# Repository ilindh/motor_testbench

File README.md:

<!-- KICAD_DIFF_GEN_START -->
<p align="center"><br><b>Top</b></p>
<p align="center"><br><b>Bottom</b></p>
<p align="center"><br><b>Dimensions</b></p>

<p align="center"><br><b>Schematic — Page 1</b></p>
<p align="center"><br><b>Load Cell And Temperature Measurements — Page 2</b></p>
<p align="center"><br><b>Power Regulation — Page 3</b></p>
<p align="center"><br><b>Voltage And Current Measurements — Page 4</b></p>

---
## 🛠 Technical Hardware Summary
*Autogenerated by GitHub Command Center*

### 📋 Project Overview
| Metric | Value |
| :--- | :--- |
| **Board Dimensions** | 99.5 x 79.51 mm |
| **Total Area** | 7910.75 mm² |
| **Layer Count** | 6 Copper Layers |
| **Total Components** | 286 |
| **SMD Components** | 244 |
| **THT Components** | 9 |
| **Unique Parts** | 72 |
| **DRC Status** | ⚠️ 26 Errors, 106 Warnings |
| **KiCad Version** | 10.0.4 |

### 📐 Manufacturing & DRC
| Metric | Value |
| :--- | :--- |
| **Vias** | 1443 Total (1443 TH, 0 Blind, 0 Micro) |

### 📄 Architecture
- **Digital Buses:** `ESP_UART_RX, ESP_UART_TX, ESP_USB_D+, ESP_USB_D-`
- **Power Domains:** `+3V3, GND, GNDREF`

### ⚙️ Mechanical
- **Mounting Holes:** 10 (H10 (MountingHole_3.2mm_M3), H9 (MountingHole_3.2mm_M3), H7 (MountingHole_3.2mm_M3), H1 (MountingHole_3.2mm_M3), H8 (MountingHole_3.2mm_M3), H6 (MountingHole_3.2mm_M3), H2 (MountingHole_3.2mm_M3), H5 (MountingHole_3.2mm_M3), H4 (MountingHole_3.2mm_M3), H3 (MountingHole_3.2mm_M3))

### 🚫 Do Not Populate (DNP)
- C100 (22u)
- C101 (22u)
- C105 (1u)
- C126 (1u)
- C60 (1u)
- C8 (1u)
- C99 (100p)
- R18 (22R)
- R40 (R)
- R41 (R)
- R59 (220R)
- R60 (220R)
- R61 (220R)
- R72 (10k)
- R73 (10k)
- R8 (22R)

### 📝 Project TODOs
- TODO: Check Min / Max stable capacitances for the LDOS
- TODO: FIND PROPER 6V 800mA INPUT TO 3V3 LDO
- TODO: MAADOITA NÄMÄ?
- TODO: TARKASTA PINOUT: TLV9001SIDBVRG4\n
- TODO: VAIHDA TÄHÄN\nMouser No:\n637-PSOT36\nMfr. No:\nPSOT36
- TODO:\n\nVARMISTA ETTÄ PINNIT JA FOOTPRINT OIKEAT:\nPJA3402_R1_00001\nSOT-23-3\n

### 🧠 Core ICs & Modules
| Reference | Component | Function / Description |
| :--- | :--- | :--- |
| IC6 | [MCP3564RT-E_ST](https://componentsearchengine.com/search.html?searchString=MCP3564RT-E/ST) | Analog to Digital Converters - ADC 24-bit delta-sigma ADC w/Vref, Quad channel, 3V |
| IC1 | [PJA3402_R1_00001](https://componentsearchengine.com/search.html?searchString=PJA3402_R1_00001) | MOSFETs 30V N-Channel Enhancement Mode MOSFET |
| U1 | ESP32-S3-WROOM-1 | RF Module, ESP32-S3 SoC, Wi-Fi 802.11b/g/n, Bluetooth, BLE, 32-bit, 3.3V, onboard antenna, SMD |
| U2 | OPA310SxDBV | Single Rail-to-Rail Input/Output Operational Amplifier with Shutdown, 1.5..5.5V supply, 3MHz GBW, 250uV offset voltage, 150mA output current, SOT-23-6 |
| U8 | TPS62933 | 3.8-30V, 3A Synchronous Buck Converters with pulse frequency modulation (PFM), SOT583-8 |
| IC4 | [AP7361C-33Y5-13](https://componentsearchengine.com/search.html?searchString=AP7361C-33Y5-13) | DIODES INC. - AP7361C-33Y5-13 - LDO, FIXED, 3.3V, 1A, -40 TO 85DEG C |
| U10 | OPA2387DR | Precision, 10-MHz, Low-Noise, Low-Power, RRIO, CMOS Operational Amplifier, SOIC-8 |
| IC3 | [NCV8184DR2G](https://componentsearchengine.com/search.html?searchString=NCV8184DR2G) | 70 mA Source Capability; Output Tracks within +/- 3m V; Low Input Voltage Tracking Performance (Works Down to Vref = 2.0 V); Low Dropout (0.35 V Typ.@50 mA); Low Quiescent Current; Thermal Shutdown; AEC Qualified; PPAP Capable |
| U14 | TPS7A2018PDBVRG4 | LDO Voltage Regulators 300-mA ultra-low-noi se low-IQ low-dropo |
| U9 | TPS62933 | 3.8-30V, 3A Synchronous Buck Converters with pulse frequency modulation (PFM), SOT583-8 |
| U18 | TPS7A2045PDBVR | LDO Voltage Regulators 300-mA ultra-low-noi se low-IQ low-dropo |
| IC5 | [MIE1W0505BGLVH-3R-P](https://componentsearchengine.com/search.html?searchString=MIE1W0505BGLVH-3R-P) | Isolated DC/DC Converters - SMD Next gen ultra small size isolated power module |
| U7 | MCP1502T-50E/CHY | Voltage References 50 ppm 0.1% Voltage Reference |
| U11 | TPS7A2055PDBVR | LDO Voltage Regulators 300-mA ultra-low-noi se low-IQ low-dropo |
| U16 | TPS7A2055PDBVR | LDO Voltage Regulators 300-mA ultra-low-noi se low-IQ low-dropo |
| U15 | TPS7A2050PDBVR | LDO Voltage Regulators 300-mA ultra-low-noi se low-IQ low-dropo |
| U13 | TPS7A2033PDBVR | TPS7A2033PDBVR |
| U17 | TPS7A2033PDBVR | LDO Voltage Regulators 300-mA ultra-low-noi se low-IQ low-dropo |
| U12 | TPS7A2050PDBVR | LDO Voltage Regulators 300-mA ultra-low-noi se low-IQ low-dropo |
| U3 | [CZ3723](https://componentsearchengine.com/search.html?searchString=CZ3A05) | Board Mount Current Sensors 60A Precise unipolar Coreless Current Sensor w/UL61800 |
| U6 | OPA2328DR | Precision, 10-MHz, Low-Noise, Low-Power, RRIO, CMOS Operational Amplifier, SOIC-8 |
| U4 | AMC1351DWV | Precision Reinforced Isolated Amplifier, 5V Input, 300 kHz Bandwidth, 0.4V/V, 0.2% Gain Tolerance, Differential Output, SOIC-8 |
| U5 | OPA2328DR | Precision Amplifiers Dual-channel precis ion 50-uV offset vo |

### 🔌 Connectors & Interfaces
| Reference | Type | Component | Description |
| :--- | :--- | :--- | :--- |
| J11 | Connector | Conn_01x04_Pin | Generic connector, single row, 01x04, script generated |
| J3 | Connector | Conn_01x07_Pin | Generic connector, single row, 01x07, script generated |
| J1 | Connector | USB_C_Receptacle_USB2.0_16P | USB 2.0-only 16P Type-C Receptacle connector |
| J2 | Connector | Conn_01x08_Pin | Generic connector, single row, 01x08, script generated |
| J10 | Connector | Conn_01x02_Pin | Generic connector, single row, 01x02, script generated |
| J7 | Connector | Conn_01x02_Pin | Generic connector, single row, 01x02, script generated |
| J8 | Connector | Conn_01x02_Pin | Generic connector, single row, 01x02, script generated |
| J6 | Connector | V_bat_secondary | Generic connector, single row, 01x02, script generated |
| J5 | Connector | [XT60PW-M](https://componentsearchengine.com/search.html?searchString=XT60PW-M) | Connector: DC supply; socket; XT60; male; PIN: 2; on PCBs; THT; 30A |
| J4 | Connector | [XT60PW-M](https://componentsearchengine.com/search.html?searchString=XT60PW-M) | Connector: DC supply; socket; XT60; male; PIN: 2; on PCBs; THT; 30A |

### 📏 Passive Components
| Component | Breakdown |
| :--- | :--- |
| Capacitor | 97x0603, 28x0805 and 1xOther |
| Diode | 2x0402, 2x0603 and 6xOther |
| Inductor | 1x1206 |
| Resistor | 73x0603 |

---
<!-- KICAD_DIFF_GEN_END -->

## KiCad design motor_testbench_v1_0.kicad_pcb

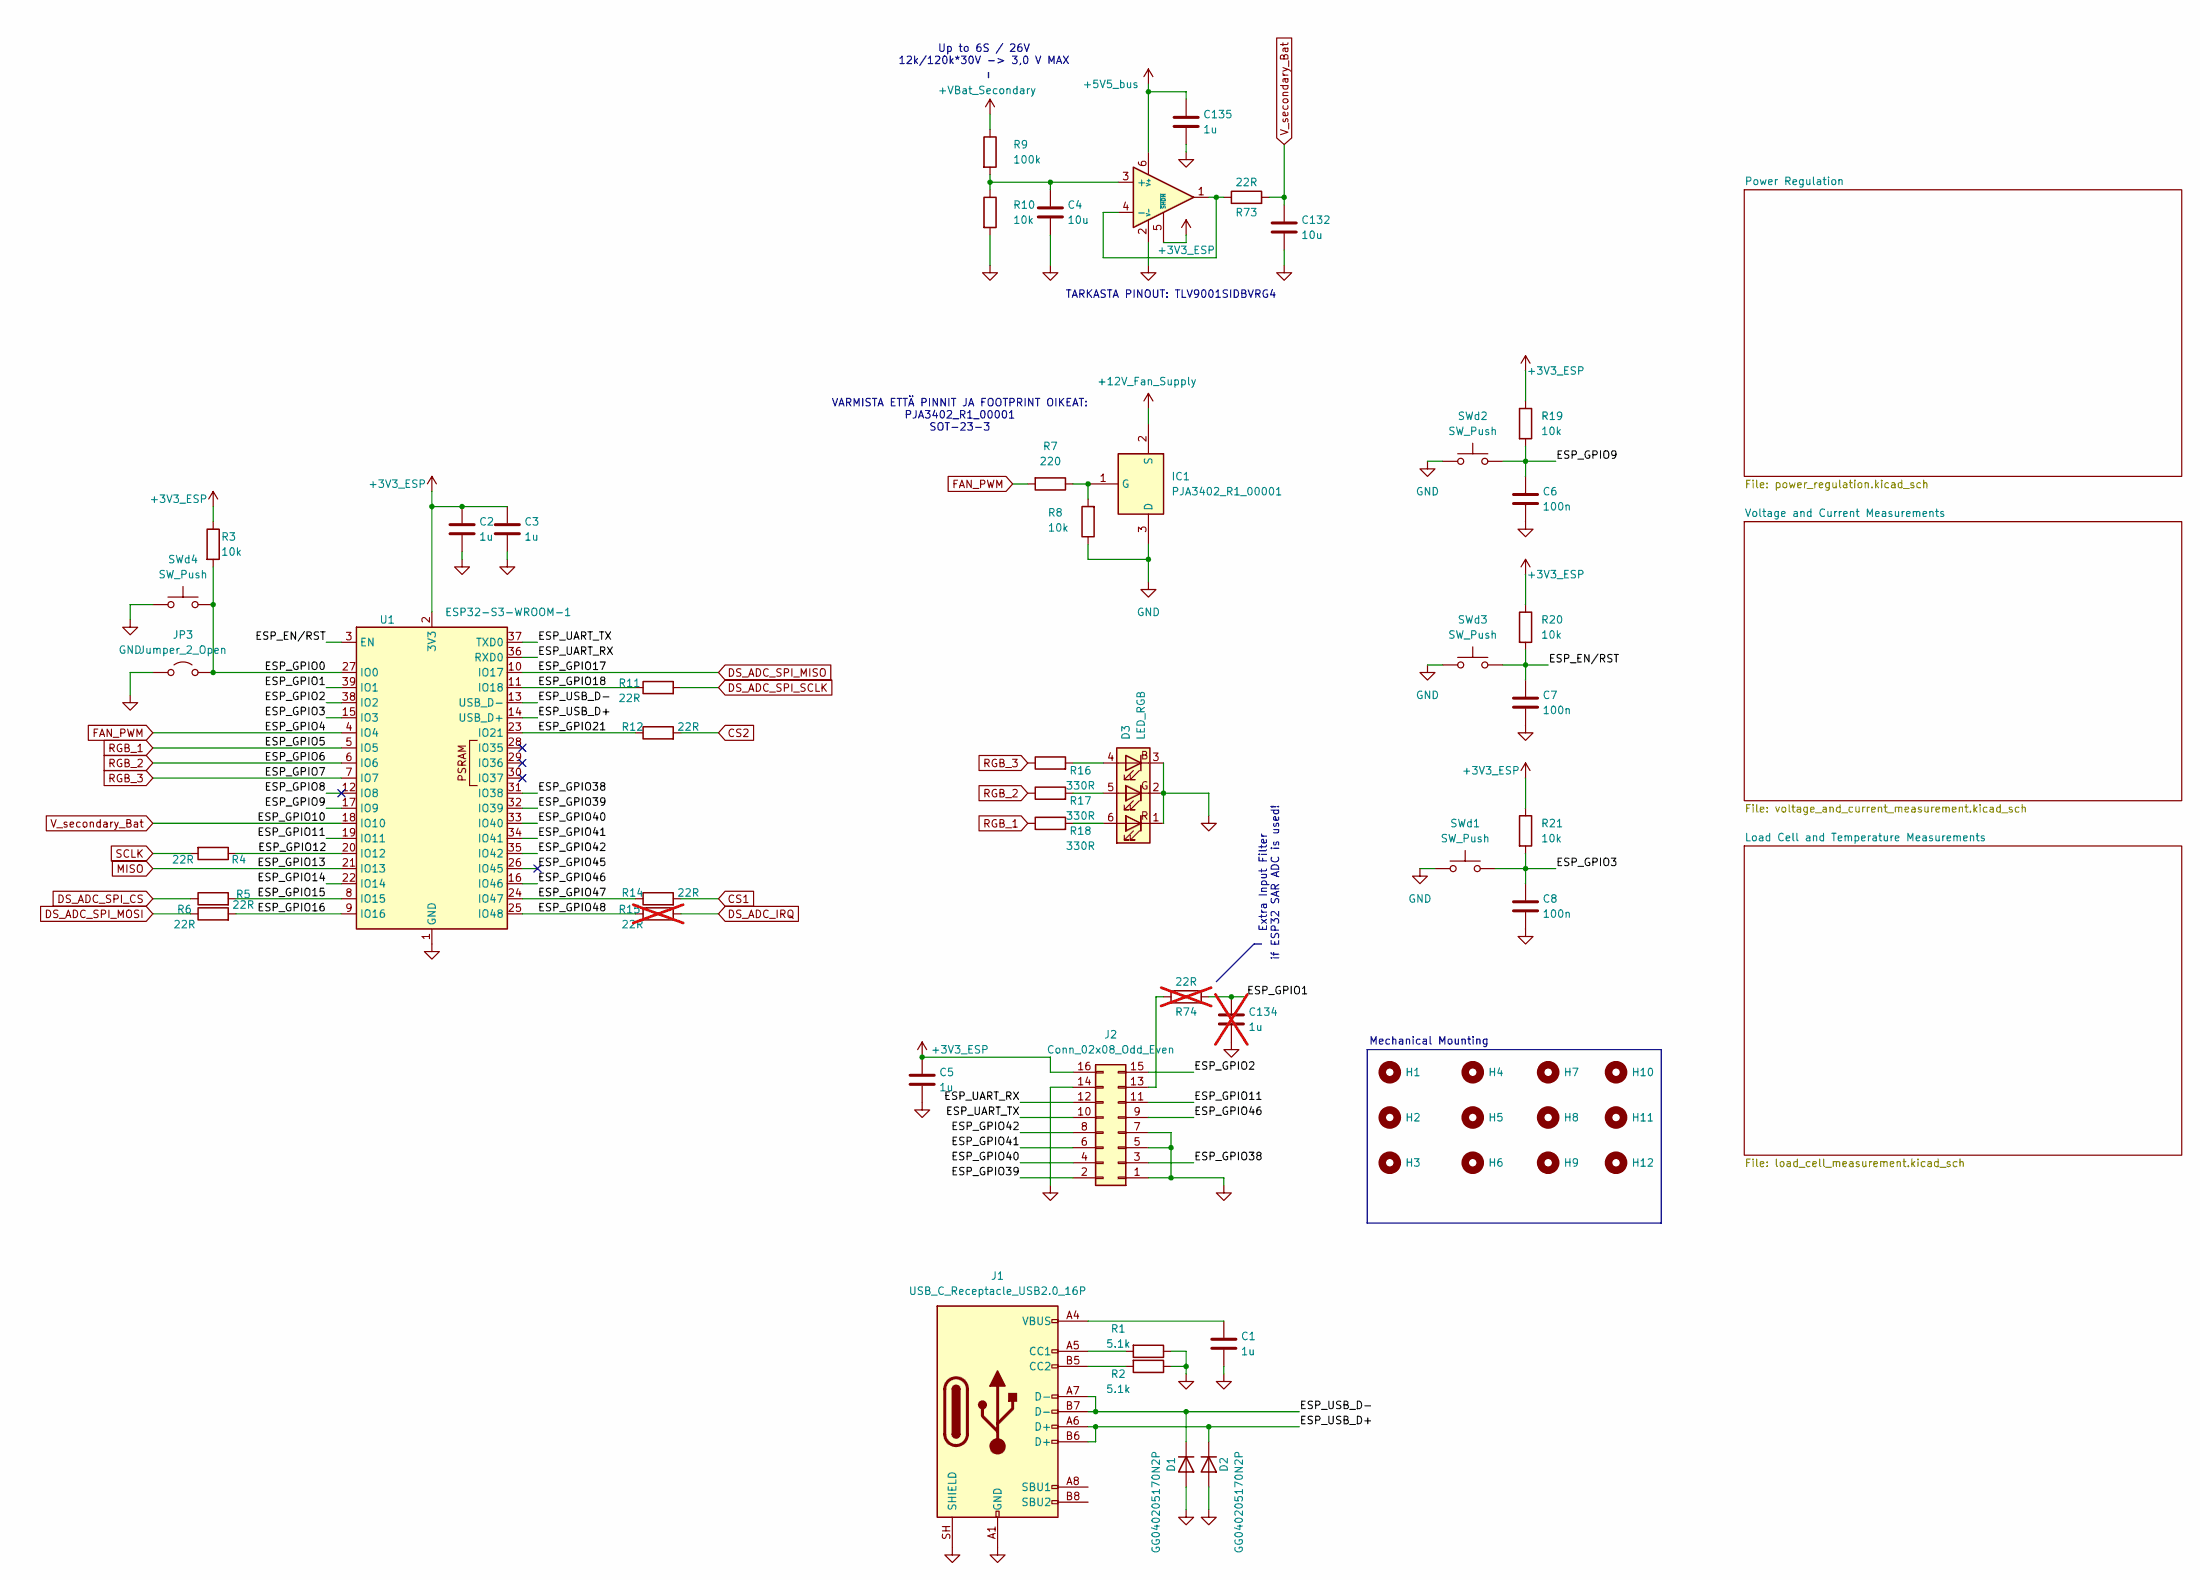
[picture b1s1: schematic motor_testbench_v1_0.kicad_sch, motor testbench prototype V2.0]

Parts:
C1, C2, C3, C5, C135: 1u; C_0603_1608Metric_Pad1.08x0.95mm_HandSolder
C4, C132: 10u; C_0603_1608Metric_Pad1.08x0.95mm_HandSolder
C6, C7, C8: 100n; C_0603_1608Metric_Pad1.08x0.95mm_HandSolder
C134: 1u; C_0603_1608Metric_Pad1.08x0.95mm_HandSolder; not fitted
D1, D2: GG040205170N2P; D_0402_1005Metric_Pad0.77x0.64mm_HandSolder
D3: LED_RGB; LED_RGB_PLCC-6
H1, H2, H3, H4, H5, H6, H7, H8, H9, H10, H11, H12: MountingHole; MountingHole_2.2mm_M2_DIN965
IC1: PJA3402_R1_00001; SOT95P240X110-3N; Manufacturer_Part_Number PJA3402_R1_00001
J1: USB_C_Receptacle_USB2.0_16P; USB_C_Receptacle_HCTL_HC-TYPE-C-16P-01A
J2: Conn_02x08_Odd_Even; PinHeader_2x08_P2.54mm_Vertical
JP3: Jumper_2_Open; SolderJumper-2_P1.3mm_Open_RoundedPad1.0x1.5mm
R1, R2: 5.1k; R_0603_1608Metric_Pad0.98x0.95mm_HandSolder
R3, R8, R10, R19, R20, R21: 10k; R_0603_1608Metric_Pad0.98x0.95mm_HandSolder
R4, R5, R6, R11, R12, R14, R73: 22R; R_0603_1608Metric_Pad0.98x0.95mm_HandSolder
R7: 220; R_0603_1608Metric_Pad0.98x0.95mm_HandSolder
R9: 100k; R_0603_1608Metric_Pad0.98x0.95mm_HandSolder
R15, R74: 22R; R_0603_1608Metric_Pad0.98x0.95mm_HandSolder; not fitted
R16, R17, R18: 330R; R_0603_1608Metric_Pad0.98x0.95mm_HandSolder
SWd1, SWd2, SWd3, SWd4: SW_Push; SW_SPST_TS-1088-xR020
U1: ESP32-S3-WROOM-1
U21: OPA310SxDBV; SOT-23-6

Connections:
+3V3_ESP: C2.1, C3.1, C5.1, J2.16, R3.1, R19.1, R20.1, R21.1, U1.2 (3V3), U21.5 (~SHDN); also elsewhere on the board
+5V5_bus: C135.1, U21.6 (V+); also elsewhere on the board
+12V_Fan_Supply: IC1.2 (S); also elsewhere on the board
+VBat_Secondary: R9.1; also elsewhere on the board
/ESP_EN/RST: C7.1, R20.2, SWd3.2, U1.3 (EN)
/ESP_GPIO0: JP3.2 (B), R3.2, SWd4.2, U1.27 (IO0)
/ESP_GPIO1: C134.1, R74.2, U1.39 (IO1)
/ESP_GPIO2: J2.15, U1.38 (IO2)
/ESP_GPIO3: C8.1, R21.2, SWd1.2, U1.15 (IO3)
/ESP_GPIO8: U1.12 (IO8)
/ESP_GPIO9: C6.1, R19.2, SWd2.2, U1.17 (IO9)
/ESP_GPIO11: J2.11, U1.19 (IO11)
/ESP_GPIO12: R4.1, U1.20 (IO12)
/ESP_GPIO14: U1.22 (IO14)
/ESP_GPIO15: R5.2, U1.8 (IO15)
/ESP_GPIO16: R6.2, U1.9 (IO16)
/ESP_GPIO18: R11.1, U1.11 (IO18)
/ESP_GPIO21: R12.1, U1.23 (IO21)
/ESP_GPIO38: J2.3, U1.31 (IO38)
/ESP_GPIO39: J2.2, U1.32 (IO39)
/ESP_GPIO40: J2.4, U1.33 (IO40)
/ESP_GPIO41: J2.6, U1.34 (IO41)
/ESP_GPIO42: J2.8, U1.35 (IO42)
/ESP_GPIO45: U1.26 (IO45)
/ESP_GPIO46: J2.9, U1.16 (IO46)
/ESP_GPIO47: R14.1, U1.24 (IO47)
/ESP_GPIO48: R15.1, U1.25 (IO48)
/ESP_UART_RX: J2.12, U1.36 (RXD0)
/ESP_UART_TX: J2.10, U1.37 (TXD0)
/ESP_USB_D+: D2.1 (K), J1.A6 (D+), J1.B6 (D+), U1.14 (USB_D+)
/ESP_USB_D-: D1.1 (K), J1.A7 (D-), J1.B7 (D-), U1.13 (USB_D-)
CS1: R14.2; also elsewhere on the board
CS2: R12.2; also elsewhere on the board
DS_ADC_IRQ: R15.2; also elsewhere on the board
DS_ADC_SPI_CS: R5.1; also elsewhere on the board
DS_ADC_SPI_MISO: U1.10 (IO17); also elsewhere on the board
DS_ADC_SPI_MOSI: R6.1; also elsewhere on the board
DS_ADC_SPI_SCLK: R11.2; also elsewhere on the board
FAN_PWM: R7.2, U1.4 (IO4)
GND: C1.2, C2.2, C3.2, C4.2, C5.2, C6.2, C7.2, C8.2, C132.2, C134.2, C135.2, D1.2 (A), D2.2 (A), D3.1 (RK), D3.2 (GK), D3.3 (BK), IC1.3 (D), J1.A1 (GND), J1.A12 (GND), J1.B1 (GND), J1.B12 (GND), J1.SH (SHIELD), J2.1, J2.5, J2.7, J2.14, JP3.1 (A), R1.1, R2.1, R8.1, R10.2, SWd1.1, SWd2.1, SWd3.1, SWd4.1, U1.1 (GND), U1.40 (GND), U1.41 (GND), U21.2 (V-); also elsewhere on the board
MISO: U1.21 (IO13); also elsewhere on the board
unnamed: C1.1, J1.A4 (VBUS), J1.A9 (VBUS), J1.B4 (VBUS), J1.B9 (VBUS)
unnamed: D3.4 (BA), R16.2
unnamed: D3.5 (GA), R17.2
unnamed: D3.6 (RA), R18.2
unnamed: IC1.1 (G), R7.1, R8.2
unnamed: J1.A5 (CC1), R1.2
unnamed: J1.B5 (CC2), R2.2
unnamed: J2.13, R74.1
unnamed: C4.1, R9.2, R10.1, U21.3 (+)
unnamed: R73.1, U21.1, U21.4 (-)
RGB_1: R18.1, U1.5 (IO5)
RGB_2: R17.1, U1.6 (IO6)
RGB_3: R16.1, U1.7 (IO7)
SCLK: R4.2; also elsewhere on the board
V_secondary_Bat: C132.1, R73.2, U1.18 (IO10)

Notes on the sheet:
Extra Input Filter if ESP32 SAR ADC is used!
Mechanical Mounting
TARKASTA PINOUT: TLV9001SIDBVRG4
VARMISTA ETTÄ PINNIT JA FOOTPRINT OIKEAT: PJA3402_R1_00001 SOT-23-3
Up to 6S / 26V 12k/120k*30V -> 3,0 V MAX

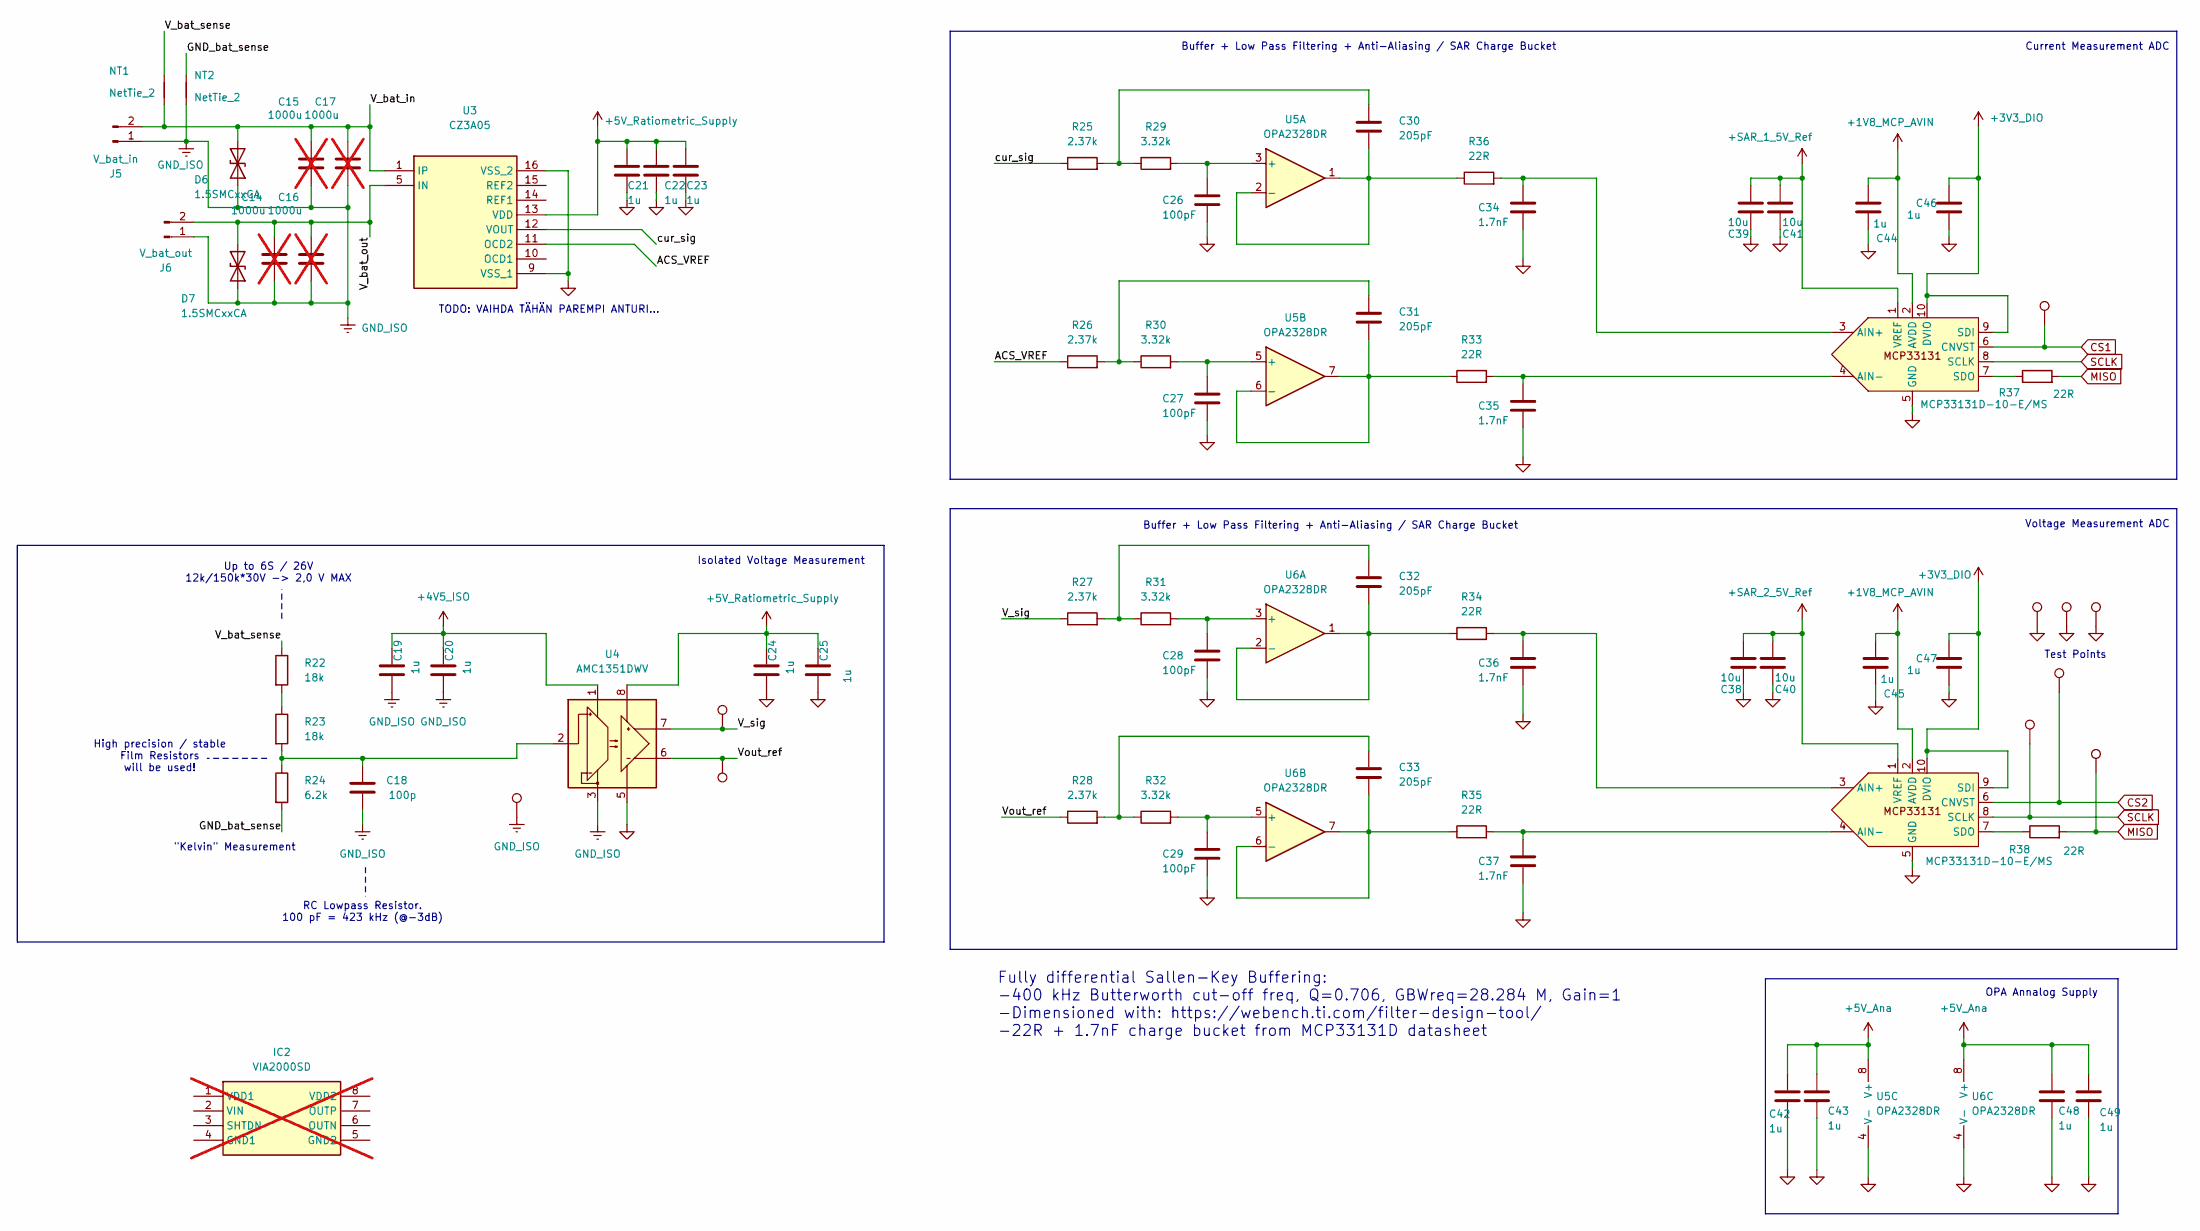
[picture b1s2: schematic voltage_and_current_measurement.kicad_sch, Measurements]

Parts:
C14, C15, C16, C17: 1000u; C_Radial_D8.0mm_H11.5mm_P3.50mm; not fitted
C18: 100p; C_0603_1608Metric_Pad1.08x0.95mm_HandSolder
C19, C20, C21, C22, C23, C24, C25, C42, C43, C44, C45, C46, C47, C48, C49: 1u; C_0603_1608Metric_Pad1.08x0.95mm_HandSolder
C26, C27, C28, C29: 100pF; C_0603_1608Metric_Pad1.08x0.95mm_HandSolder
C30, C31, C32, C33: 205pF; C_0603_1608Metric_Pad1.08x0.95mm_HandSolder
C34, C35, C36, C37: 1.7nF; C_0603_1608Metric_Pad1.08x0.95mm_HandSolder
C38, C39, C40, C41: 10u; C_0603_1608Metric_Pad1.08x0.95mm_HandSolder
CS1, CS2: TestPoint; TestPoint_Pad_D1.0mm
D6, D7: 1.5SMCxxCA; D_SMC
Dout1: TestPoint; TestPoint_Pad_D1.0mm
GND1, GND2, GND3, GND4: TestPoint; TestPoint_Pad_D1.0mm
IC2: VIA2000SD; SOIC127P1150X280-8N; Manufacturer_Part_Number VIA2000SD; not fitted
J5: V_bat_in; AMASS_XT60PW-M_1x02_P7.20mm_Horizontal_with3DModel
J6: V_bat_out; AMASS_XT60PW-M_1x02_P7.20mm_Horizontal_with3DModel
MCP1, MCP2: MCP33131D-10-E/MS; MSOP-10_3x3mm_P0.5mm
NT1, NT2: NetTie_2; NetTie-2_SMD_Pad0.5mm
R22, R23: 18k; R_0603_1608Metric_Pad0.98x0.95mm_HandSolder
R24: 6.2k; R_0603_1608Metric_Pad0.98x0.95mm_HandSolder
R25, R26, R27, R28: 2.37k; R_0603_1608Metric_Pad0.98x0.95mm_HandSolder
R29, R30, R31, R32: 3.32k; R_0603_1608Metric_Pad0.98x0.95mm_HandSolder
R33, R34, R35, R36, R37, R38: 22R; R_0603_1608Metric_Pad0.98x0.95mm_HandSolder
SCLK1: TestPoint; TestPoint_Pad_D1.0mm
U3: CZ3A05; Manufacturer_Part_Number CZ3A05; Mouser Part Number 412-CZ3A05
U4: AMC1351DWV; SOIC-8_7.5x5.85mm_P1.27mm
U5: OPA2328DR; SOIC-8_3.9x4.9mm_P1.27mm
U6: OPA2328DR; SOIC-8_3.9x4.9mm_P1.27mm; Mouser No: 595-OPA2328DR
Vsig1, Vsig2: TestPoint; TestPoint_Pad_D1.0mm

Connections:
+1V8_MCP_AVIN: C44.2, C45.2, MCP1.2 (AVDD), MCP2.2 (AVDD); also elsewhere on the board
+3V3_DIO: C46.1, C47.1, MCP1.9 (SDI), MCP1.10 (DVIO), MCP2.9 (SDI), MCP2.10 (DVIO); also elsewhere on the board
+4V5_ISO: C19.1, C20.1, U4.1 (VDD1); also elsewhere on the board
+5V_Ana: C42.1, C43.1, C48.1, C49.1, U5.8 (V+), U6.8 (V+); also elsewhere on the board
+5V_Ratiometric_Supply: C21.1, C22.1, C23.1, C24.1, C25.1, U3.13 (VDD), U4.8 (VDD2); also elsewhere on the board
+SAR_1_5V_Ref: C39.1, C41.1, MCP1.1 (VREF); also elsewhere on the board
+SAR_2_5V_Ref: C38.1, C40.1, MCP2.1 (VREF); also elsewhere on the board
/Voltage and Current Measurements/ACS_VREF: R26.1, U3.11 (OCD2); also elsewhere on the board
/Voltage and Current Measurements/GND_bat_sense: NT2.2, R24.2
/Voltage and Current Measurements/V_bat_in: C15.1, C17.1, D6.2 (A2), J5.2, NT1.1, U3.1 (IP)
/Voltage and Current Measurements/V_bat_out: C14.1, C16.1, D7.2 (A2), J6.2, U3.5 (IN)
/Voltage and Current Measurements/V_bat_sense: NT1.2, R22.1
/Voltage and Current Measurements/V_sig: R27.1, U4.7 (OUTP), Vsig1.1 (1_1)
/Voltage and Current Measurements/Vout_ref: R28.1, U4.6 (OUTN), Vsig2.1 (1_1)
/Voltage and Current Measurements/cur_sig: R25.1, U3.12 (VOUT); also elsewhere on the board
CS1: CS1.1 (1_1), MCP1.6 (CNVST); also elsewhere on the board
CS2: CS2.1 (1_1), MCP2.6 (CNVST); also elsewhere on the board
GND: C21.2, C22.2, C23.2, C24.2, C25.2, C26.2, C27.2, C28.2, C29.2, C34.2, C35.2, C36.2, C37.2, C38.2, C39.2, C40.2, C41.2, C42.2, C43.2, C44.1, C45.1, C46.2, C47.2, C48.2, C49.2, GND2.1 (1_1), GND3.1 (1_1), GND4.1 (1_1), MCP1.5 (GND), MCP2.5 (GND), U3.9 (VSS_1), U3.16 (VSS_2), U4.5 (GND2), U5.4 (V-), U6.4 (V-); also elsewhere on the board
GND_ISO: C14.2, C15.2, C16.2, C17.2, C18.2, C19.2, C20.2, D6.1 (A1), D7.1 (A1), GND1.1 (1_1), J5.1, J6.1, NT2.1, U4.3 (GND1), U4.4 (GND1); also elsewhere on the board
MISO: Dout1.1 (1_1), R37.2, R38.2; also elsewhere on the board
unnamed: C30.1, R25.2, R29.1
unnamed: C31.1, R26.2, R30.1
unnamed: C32.1, R27.2, R31.1
unnamed: C33.1, R28.2, R32.1
unnamed: C34.1, MCP1.3 (AIN+), R36.2
unnamed: C35.1, MCP1.4 (AIN-), R33.2
unnamed: MCP1.7 (SDO), R37.1
unnamed: C36.1, MCP2.3 (AIN+), R34.2
unnamed: C37.1, MCP2.4 (AIN-), R35.2
unnamed: MCP2.7 (SDO), R38.1
unnamed: R22.2, R23.1
unnamed: C18.1, R23.2, R24.1, U4.2 (IN)
unnamed: C26.1, R29.2, U5.3 (+)
unnamed: C30.2, R36.1, U5.1, U5.2 (-)
unnamed: C27.1, R30.2, U5.5 (+)
unnamed: C31.2, R33.1, U5.6 (-), U5.7
unnamed: C28.1, R31.2, U6.3 (+)
unnamed: C32.2, R34.1, U6.1, U6.2 (-)
unnamed: C29.1, R32.2, U6.5 (+)
unnamed: C33.2, R35.1, U6.6 (-), U6.7
SCLK: MCP1.8 (SCLK), MCP2.8 (SCLK), SCLK1.1 (1_1); also elsewhere on the board

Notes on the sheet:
RC Lowpass Resistor. 100 pF = 423 kHz (@-3dB)
TODO: VAIHDA TÄHÄN PAREMPI ANTURI...
Up to 6S / 26V 12k/150k*30V -> 2,0 V MAX
OPA Annalog Supply
Voltage Measurement ADC
Buffer + Low Pass Filtering + Anti-Aliasing / SAR Charge Bucket
Isolated Voltage Measurement
Current Measurement ADC
Test Points
High precision / stable Film Resistors will be used!
Fully differential Sallen-Key Buffering: -400 kHz Butterworth cut-off freq, Q=0.706, GBWreq=28.284 M, Gain=1 -Dimensioned with: https://webench.ti.com/filter-design-tool/ -22R + 1.7nF charge bucket from MCP33131D datasheet
"Kelvin" Measurement

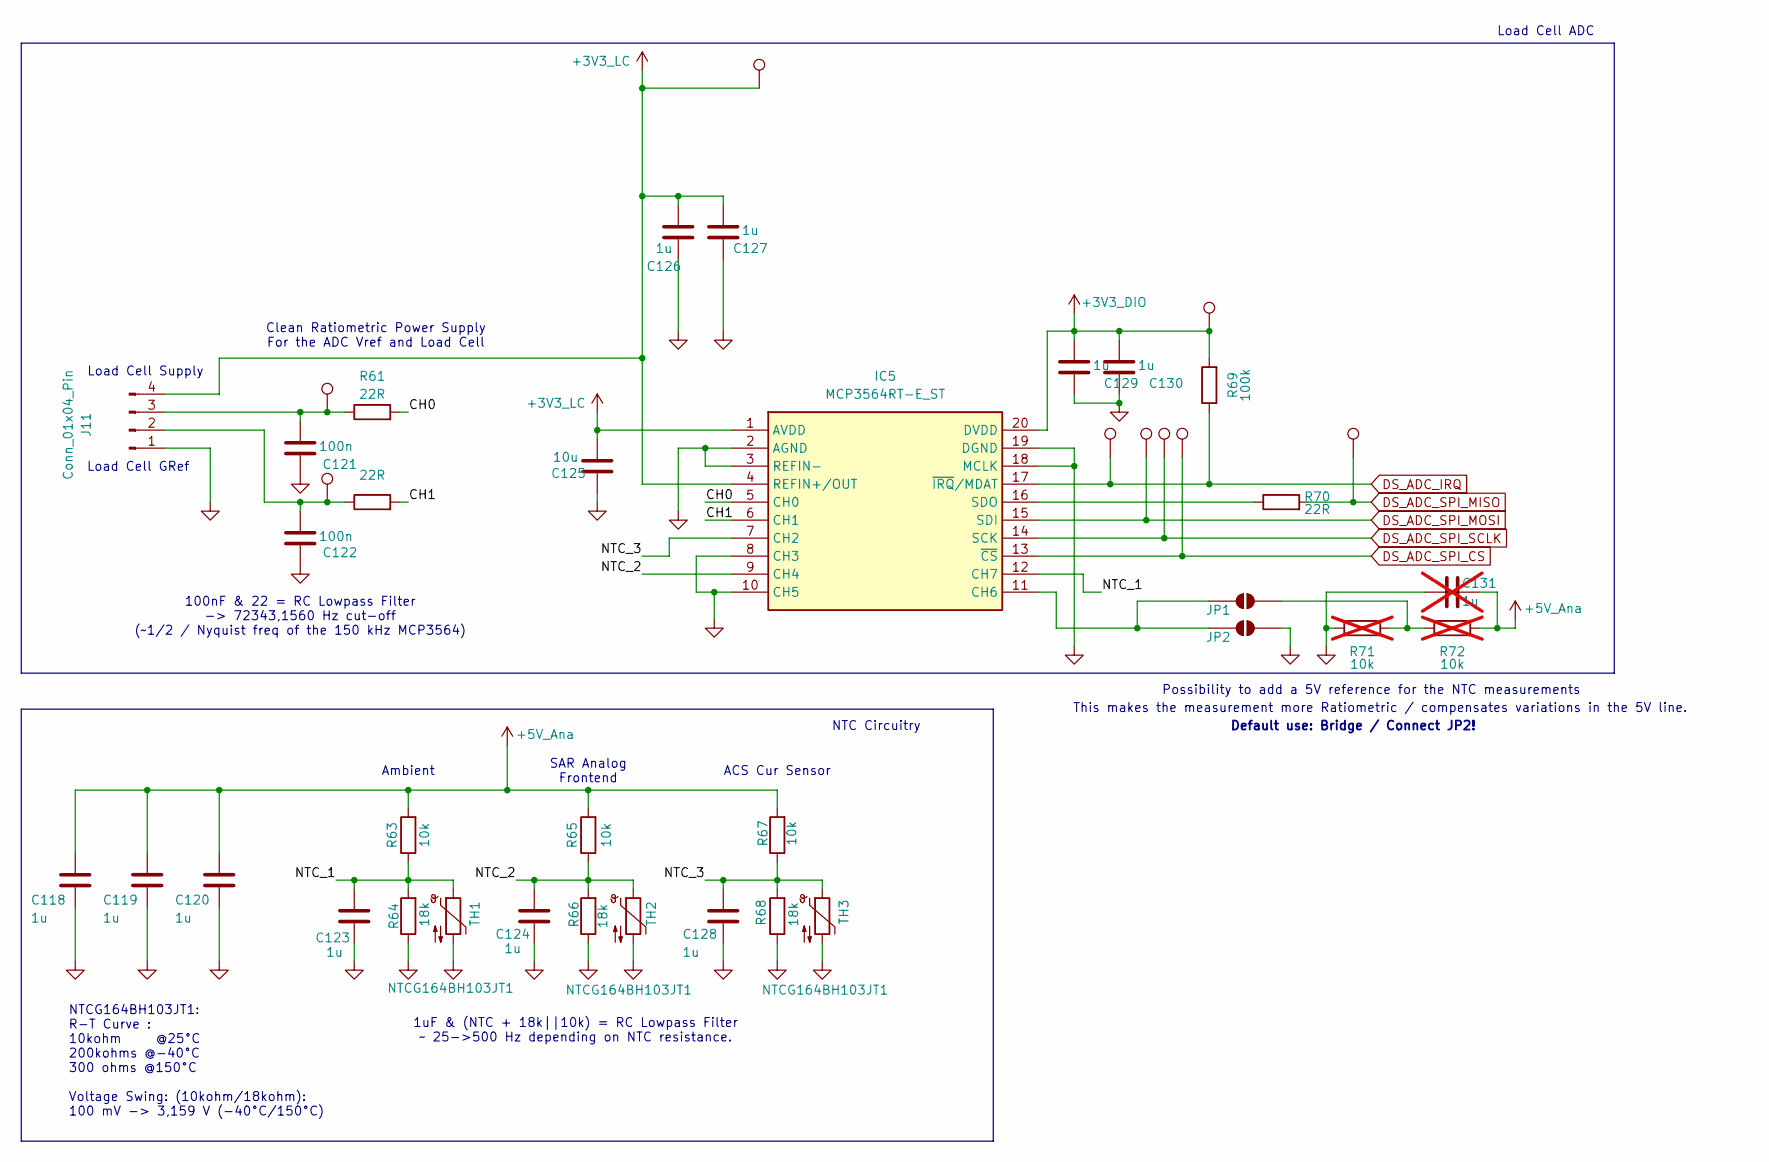
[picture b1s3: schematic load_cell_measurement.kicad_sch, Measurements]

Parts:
C118, C119, C120, C123, C124, C126, C127, C128, C129, C130: 1u; C_0603_1608Metric_Pad1.08x0.95mm_HandSolder
C121, C122: 100n; C_0603_1608Metric_Pad1.08x0.95mm_HandSolder
C125: 10u; C_0603_1608Metric_Pad1.08x0.95mm_HandSolder
C131: 1u; C_0603_1608Metric_Pad1.08x0.95mm_HandSolder; not fitted
I1, I2, I3, I5, I6, I7, I8, I9, I10: TestPoint; TestPoint_Pad_D1.0mm
IC5: MCP3564RT-E_ST; SOP65P640X120-20N; Manufacturer_Part_Number MCP3564RT-E/ST; Mouser Part Number 579-MCP3564RT-E/ST
J11: Conn_01x04_Pin; PinHeader_1x04_P2.54mm_Vertical
JP1, JP2: SolderJumper_2_Open; SolderJumper-2_P1.3mm_Open_RoundedPad1.0x1.5mm
R61, R62, R70: 22R; R_0603_1608Metric_Pad0.98x0.95mm_HandSolder
R63, R65, R67: 10k; R_0603_1608Metric_Pad0.98x0.95mm_HandSolder
R64, R66, R68: 18k; R_0603_1608Metric_Pad0.98x0.95mm_HandSolder
R69: 100k; R_0603_1608Metric_Pad0.98x0.95mm_HandSolder
R71, R72: 10k; R_0603_1608Metric_Pad0.98x0.95mm_HandSolder; not fitted
TH1, TH2, TH3: NTCG164BH103JT1; R_0603_1608Metric_Pad0.98x0.95mm_HandSolder

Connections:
+3V3_DIO: C129.2, C130.2, I9.1 (1_1), IC5.20 (DVDD), R69.2; also elsewhere on the board
+3V3_LC: C125.2, C126.2, C127.2, I3.1 (1_1), IC5.1 (AVDD), IC5.4 (REFIN+/OUT), J11.4; also elsewhere on the board
+5V_Ana: C118.1, C119.1, C120.1, C131.2, R63.2, R65.2, R67.2, R72.2; also elsewhere on the board
/Load Cell and Temperature Measurements/CH0: IC5.5 (CH0), R61.2
/Load Cell and Temperature Measurements/CH1: IC5.6 (CH1), R62.2
/Load Cell and Temperature Measurements/NTC_1: C123.1, IC5.12 (CH7), R63.1, R64.2, TH1.1
/Load Cell and Temperature Measurements/NTC_2: C124.1, IC5.9 (CH4), R65.1, R66.2, TH2.1
/Load Cell and Temperature Measurements/NTC_3: C128.1, IC5.7 (CH2), R67.1, R68.2, TH3.1
DS_ADC_IRQ: I5.1 (1_1), IC5.17 (~IRQ/MDAT), R69.1; also elsewhere on the board
DS_ADC_SPI_CS: I8.1 (1_1), IC5.13 (~CS); also elsewhere on the board
DS_ADC_SPI_MISO: I10.1 (1_1), R70.2; also elsewhere on the board
DS_ADC_SPI_MOSI: I6.1 (1_1), IC5.15 (SDI); also elsewhere on the board
DS_ADC_SPI_SCLK: I7.1 (1_1), IC5.14 (SCK); also elsewhere on the board
GND: C118.2, C119.2, C120.2, C121.1, C122.1, C123.2, C124.2, C125.1, C126.1, C127.1, C128.2, C129.1, C130.1, C131.1, IC5.2 (AGND), IC5.3 (REFIN-), IC5.8 (CH3), IC5.10 (CH5), IC5.18 (MCLK), IC5.19 (DGND), J11.1, JP2.2 (B), R64.1, R66.1, R68.1, R71.1, TH1.2, TH2.2, TH3.2; also elsewhere on the board
unnamed: IC5.11 (CH6), JP1.1 (A), JP2.1 (A)
unnamed: IC5.16 (SDO), R70.1
unnamed: C122.2, I2.1 (1_1), J11.2, R62.1
unnamed: C121.2, I1.1 (1_1), J11.3, R61.1
unnamed: JP1.2 (B), R71.2, R72.1

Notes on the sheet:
100nF & 22 = RC Lowpass Filter -> 72343,1560 Hz cut-off (~1/2 / Nyquist freq of the 150 kHz MCP3564)
SAR Analog Frontend
Default use: Bridge / Connect JP2!
NTC Circuitry
NTCG164BH103JT1: R-T Curve : 10kohm @25°C 200kohms @-40°C 300 ohms @150°C Voltage Swing: (10kohm/18kohm): 100 mV -> 3,159 V (-40°C/150°C)
ACS Cur Sensor
Clean Ratiometric Power Supply For the ADC Vref and Load Cell
This makes the measurement more Ratiometric / compensates variations in the 5V line.
Load Cell GRef
Load Cell ADC
Ambient
Possibility to add a 5V reference for the NTC measurements
1uF & (NTC + 18k||10k) = RC Lowpass Filter ~ 25->500 Hz depending on NTC resistance.
Load Cell Supply
